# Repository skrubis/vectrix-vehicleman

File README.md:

# vectrix-vehicleman
Vectrix VX1 BMS manager + TC charger control + LTE connectivity + GPS tracker + Alarm + whatever else time can solve.

meant to be used together with Openinverter Flying ADC BMS

Includes:

 - ESP32 + SD card
  - Battery backup with charger for esp + LTE (1x18650)
   - Footprint for GigaVESC HV (150-180V?)@2~3A(?) -> 12V [DCDC](https://github.com/kaminaris/GigaESC/tree/master/PowerBoard/TL494V2OC)
   - LTE modem (SIM7070G with GNSS) + 1 SIM
   - 1x CAN TWAI transceiver
   - 2x CAN SPI transceiver (in case TC charger(s) are on the same address or say multiple R4850G2 are used)
   - A few relays and mosfets for external loads
   - Accelerometer/IMU for "alarm" functionality
   - Moisture/temp sensor for condensation detection (?)
   - RTC
   -TYPE 2 charging CP PP control
   - External antenna PCB for active GNSS + passive LTE should be here as well.

NOT TESTED, NOT VERIFIED!
CC-BY-NC 4.0

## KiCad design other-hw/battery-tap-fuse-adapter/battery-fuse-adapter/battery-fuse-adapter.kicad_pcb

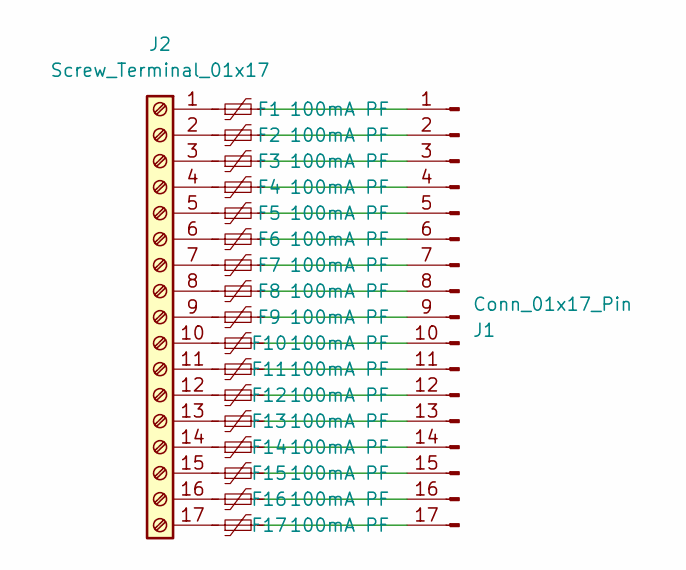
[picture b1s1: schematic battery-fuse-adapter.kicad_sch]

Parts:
F1, F2, F3, F4, F5, F6, F7, F8, F9, F10, F11, F12, F13, F14, F15, F16, F17: 100mA PF; Fuse_0603_1608Metric; LCSC C369142
J1: Conn_01x17_Pin; PinHeader_1x17_P2.54mm_Vertical
J2: Screw_Terminal_01x17; C430372; LCSC C430372

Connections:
unnamed: F1.2, J1.1
unnamed: F2.2, J1.2
unnamed: F3.2, J1.3
unnamed: F4.2, J1.4
unnamed: F5.2, J1.5
unnamed: F6.2, J1.6
unnamed: F7.2, J1.7
unnamed: F8.2, J1.8
unnamed: F9.2, J1.9
unnamed: F10.2, J1.10
unnamed: F11.2, J1.11
unnamed: F12.2, J1.12
unnamed: F13.2, J1.13
unnamed: F14.2, J1.14
unnamed: F15.2, J1.15
unnamed: F16.2, J1.16
unnamed: F17.2, J1.17
unnamed: F1.1, J2.1
unnamed: F2.1, J2.2
unnamed: F3.1, J2.3
unnamed: F4.1, J2.4
unnamed: F5.1, J2.5
unnamed: F6.1, J2.6
unnamed: F7.1, J2.7
unnamed: F8.1, J2.8
unnamed: F9.1, J2.9
unnamed: F10.1, J2.10
unnamed: F11.1, J2.11
unnamed: F12.1, J2.12
unnamed: F13.1, J2.13
unnamed: F14.1, J2.14
unnamed: F15.1, J2.15
unnamed: F16.1, J2.16
unnamed: F17.1, J2.17

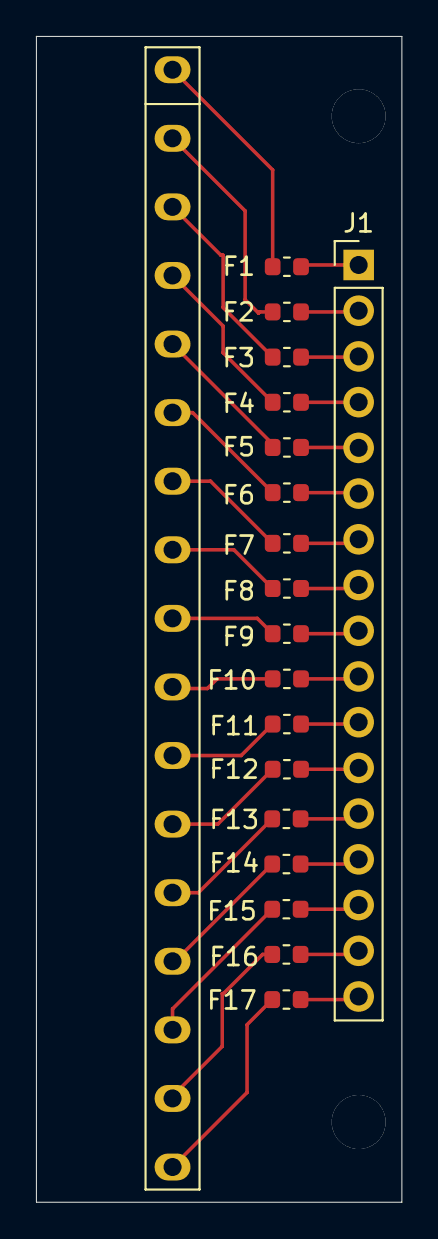
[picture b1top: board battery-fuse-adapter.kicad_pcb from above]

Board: 2 copper layers, 20.3 x 64.8 mm, 19 parts (0 on the bottom side), 34 nets.

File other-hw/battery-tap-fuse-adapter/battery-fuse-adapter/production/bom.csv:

Designator,Footprint,Quantity,Value,LCSC Part #
"F1, F10, F11, F12, F13, F14, F15, F16, F17, F2, F3, F4, F5, F6, F7, F8, F9",0603,17,100mA PF,C369142
J2,C430372,1,Screw_Terminal_01x17,C430372

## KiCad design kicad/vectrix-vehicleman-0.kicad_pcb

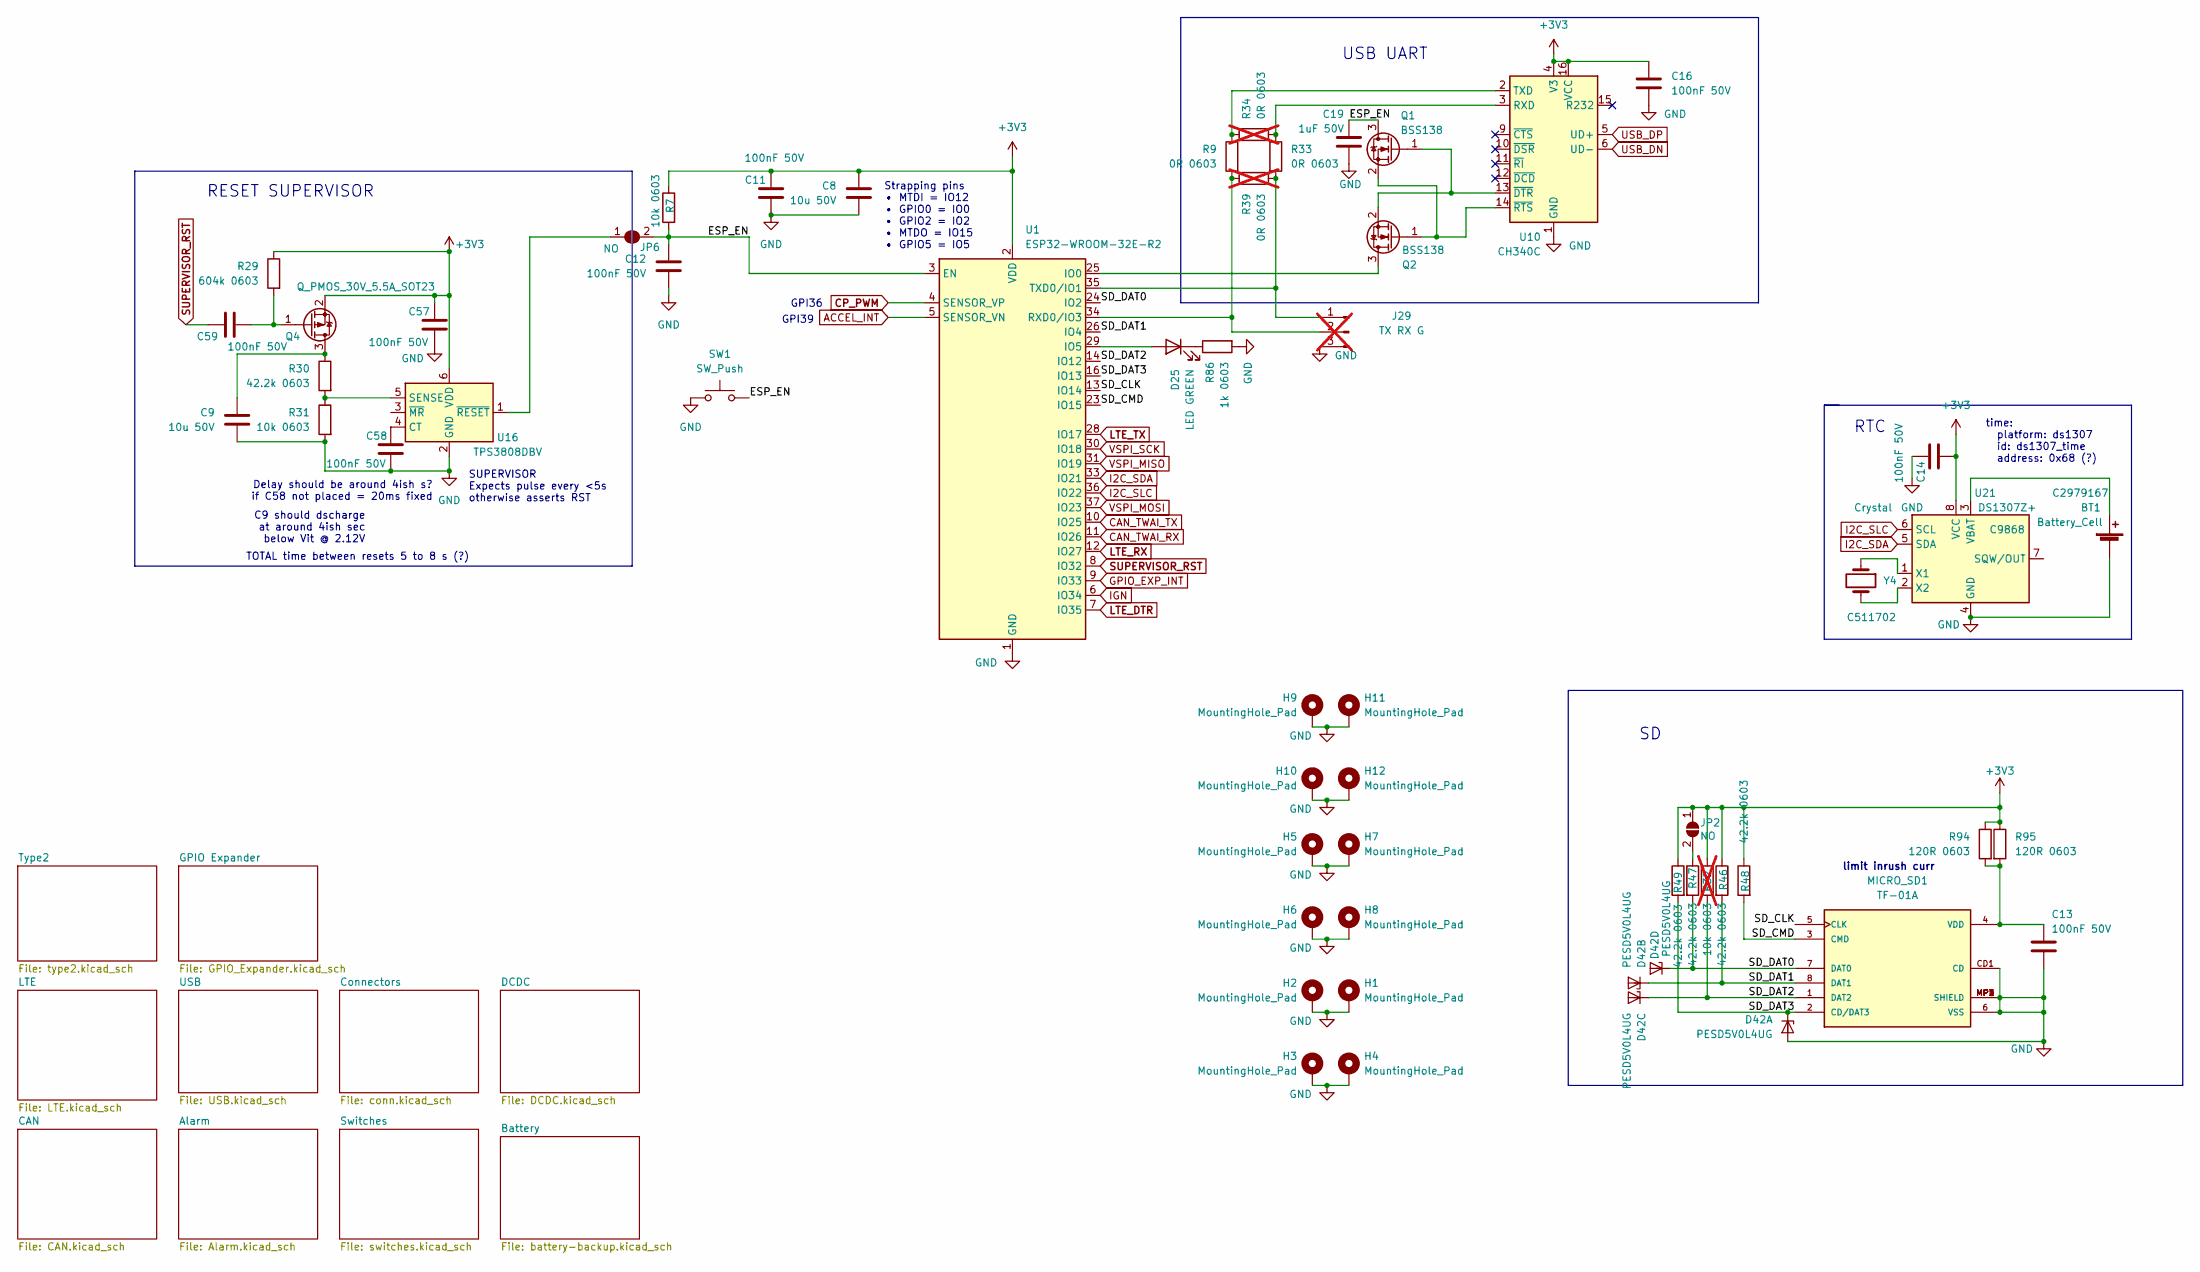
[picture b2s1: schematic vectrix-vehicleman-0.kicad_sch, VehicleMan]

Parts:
BT1: Battery_Cell; BatteryHolder_MYOUNG_BS-07-A1BJ001_CR2032; LCSC C2979167
C8, C9: 10u 50V; C_1206_3216Metric; LCSC C13585
C11, C12, C13, C14, C16, C57, C58, C59: 100nF 50V; C_0603_1608Metric; LCSC C14663
C19: 1uF 50V; C_0603_1608Metric; LCSC C6119852
D25: LED GREEN; LED_0805_2012Metric; LCSC C5875740
D42: PESD5V0L4UG; SOT-353_SC-70-5; LCSC C5116450
H1, H2, H3, H4, H5, H6, H7, H8, H9, H10, H11, H12: MountingHole_Pad; MountingHole_3.2mm_M3_DIN965_Pad_TopBottom
J29: TX RX G; PinHeader_1x03_P1.27mm_Vertical; not fitted
JP2, JP6: NO; SolderJumper-2_P1.3mm_Open_TrianglePad1.0x1.5mm
MICRO_SD1: TF-01A; LCSC C91145
Q1, Q2: BSS138; SOT-23; LCSC C112239
Q4: Q_PMOS_30V_5.5A_SOT23; SOT-23; LCSC C105162
R7, R31: 10k 0603; R_0603_1608Metric; LCSC C2930027
R9, R33: 0R 0603; R_0603_1608Metric; LCSC C21189
R29: 604k 0603; R_0603_1608Metric; LCSC C2933246
R30, R46, R47, R48, R49: 42.2k 0603; R_0603_1608Metric; LCSC C5126245
R32: 10k 0603; R_0603_1608Metric; LCSC C2930027; not fitted
R34, R39: 0R 0603; R_0603_1608Metric; LCSC C21189; not fitted
R86: 1k 0603; R_0603_1608Metric; LCSC C2907113
R94, R95: 120R 0603; R_0603_1608Metric; LCSC C22787
SW1: SW_Push; SW_PUSH_6mm; LCSC C455095
U1: ESP32-WROOM-32E-R2; ESP32-WROOM-32D; LCSC C82899
U10: CH340C; SOIC-16_3.9x9.9mm_P1.27mm; LCSC C84681
U16: TPS3808DBV; SOT-23-6; LCSC C19653
U21: DS1307Z+; SOIC-8_3.9x4.9mm_P1.27mm; LCSC C9868
Y4: Crystal; Crystal_DS26_D2.0mm_L6.0mm_Horizontal; LCSC C511702

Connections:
+3V3: C8.1, C11.1, C14.2, C16.1, C57.1, JP2.1 (A), Q4.2 (S), R7.1, R29.1, R32.1, R46.1, R48.1, R49.1, R94.1, R95.1, U1.2 (VDD), U10.4 (V3), U10.16 (VCC), U16.6 (VDD), U21.8 (VCC); also elsewhere on the board
/ESP_EN: C12.1, C19.1, JP6.2 (B), Q1.3 (D), R7.2, SW1.2, U1.3 (EN)
/SD_CLK: MICRO_SD1.5 (CLK), U1.13 (IO14)
/SD_CMD: MICRO_SD1.3 (CMD), R48.2, U1.23 (IO15)
/SD_DAT0: D42.5 (K4), MICRO_SD1.7 (DAT0), R47.2, U1.24 (IO2)
/SD_DAT1: D42.3 (K2), MICRO_SD1.8 (DAT1), R46.2, U1.26 (IO4)
/SD_DAT2: D42.4 (K3), MICRO_SD1.1 (DAT2), R32.2, U1.14 (IO12)
/SD_DAT3: D42.1 (K1), MICRO_SD1.2 (CD/DAT3), R49.2, U1.16 (IO13)
ACCEL_INT: U1.5 (SENSOR_VN); also elsewhere on the board
CAN_TWAI_RX: U1.11 (IO26); also elsewhere on the board
CAN_TWAI_TX: U1.10 (IO25); also elsewhere on the board
CP_PWM: U1.4 (SENSOR_VP); also elsewhere on the board
GND: BT1.2 (-), C8.2, C9.2, C11.2, C12.2, C13.2, C14.1, C16.2, C19.2, C57.2, C58.2, D42.2 (A), H1.1, H2.1, H3.1, H4.1, H5.1, H6.1, H7.1, H8.1, H9.1, H10.1, H11.1, H12.1, J29.3, MICRO_SD1.6 (VSS), MICRO_SD1.CD1 (CD), MICRO_SD1.MP1 (SHIELD), MICRO_SD1.MP2 (SHIELD), MICRO_SD1.MP3 (SHIELD), MICRO_SD1.MP4 (SHIELD), R31.2, R86.2, SW1.1, U1.1 (GND), U1.15 (GND), U1.38 (GND), U1.39 (GND), U10.1 (GND), U16.2 (GND), U21.4 (GND); also elsewhere on the board
GPIO_EXP_INT: U1.9 (IO33); also elsewhere on the board
I2C_SDA: U1.33 (IO21), U21.5 (SDA); also elsewhere on the board
I2C_SLC: U1.36 (IO22), U21.6 (SCL); also elsewhere on the board
IGN: U1.6 (IO34); also elsewhere on the board
LTE_DTR: U1.7 (IO35); also elsewhere on the board
LTE_RX: U1.12 (IO27); also elsewhere on the board
LTE_TX: U1.28 (IO17); also elsewhere on the board
unnamed: BT1.1 (+), U21.3 (VBAT)
unnamed: D25.2 (A), U1.29 (IO5)
unnamed: D25.1 (K), R86.1
unnamed: J29.1, R33.2, R39.2, U1.35 (TXD0/IO1)
unnamed: J29.2, R9.2, R39.1, U1.34 (RXD0/IO3)
unnamed: JP2.2 (B), R47.1
unnamed: JP6.1 (A), U16.1 (~RESET)
unnamed: C13.1, MICRO_SD1.4 (VDD), R94.2, R95.2
unnamed: Q1.1 (G), Q2.2 (S), U10.13 (~DTR)
unnamed: Q1.2 (S), Q2.1 (G), U10.14 (~RTS)
unnamed: Q2.3 (D), U1.25 (IO0)
unnamed: C9.1, Q4.3 (D), R30.1
unnamed: C59.2, Q4.1 (G), R29.2
unnamed: R33.1, R34.2, U10.3 (RXD)
unnamed: R9.1, R34.1, U10.2 (TXD)
unnamed: C58.1, U16.4 (CT)
unnamed: R30.2, R31.1, U16.5 (SENSE)
unnamed: U21.1 (X1), Y4.1
unnamed: U21.2 (X2), Y4.2
SUPERVISOR_RST: C59.1, U1.8 (IO32)
USB_DN: U10.6 (UD-); also elsewhere on the board
USB_DP: U10.5 (UD+); also elsewhere on the board
VSPI_MISO: U1.31 (IO19); also elsewhere on the board
VSPI_MOSI: U1.37 (IO23); also elsewhere on the board
VSPI_SCK: U1.30 (IO18); also elsewhere on the board

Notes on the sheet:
C9 should dscharge at around 4ish sec below Vit @ 2.12V
SUPERVISOR Expects pulse every <5s otherwise asserts RST
limit inrush curr
TOTAL time between resets 5 to 8 s (?)
RTC
GPI39
GPI36
USB UART
RESET SUPERVISOR
Strapping pins • MTDI = IO12 • GPIO0 = IO0 • GPIO2 = IO2 • MTDO = IO15 • GPIO5 = IO5
time: platform: ds1307 id: ds1307_time address: 0x68 (?)
Delay should be around 4ish s? if C58 not placed = 20ms fixed

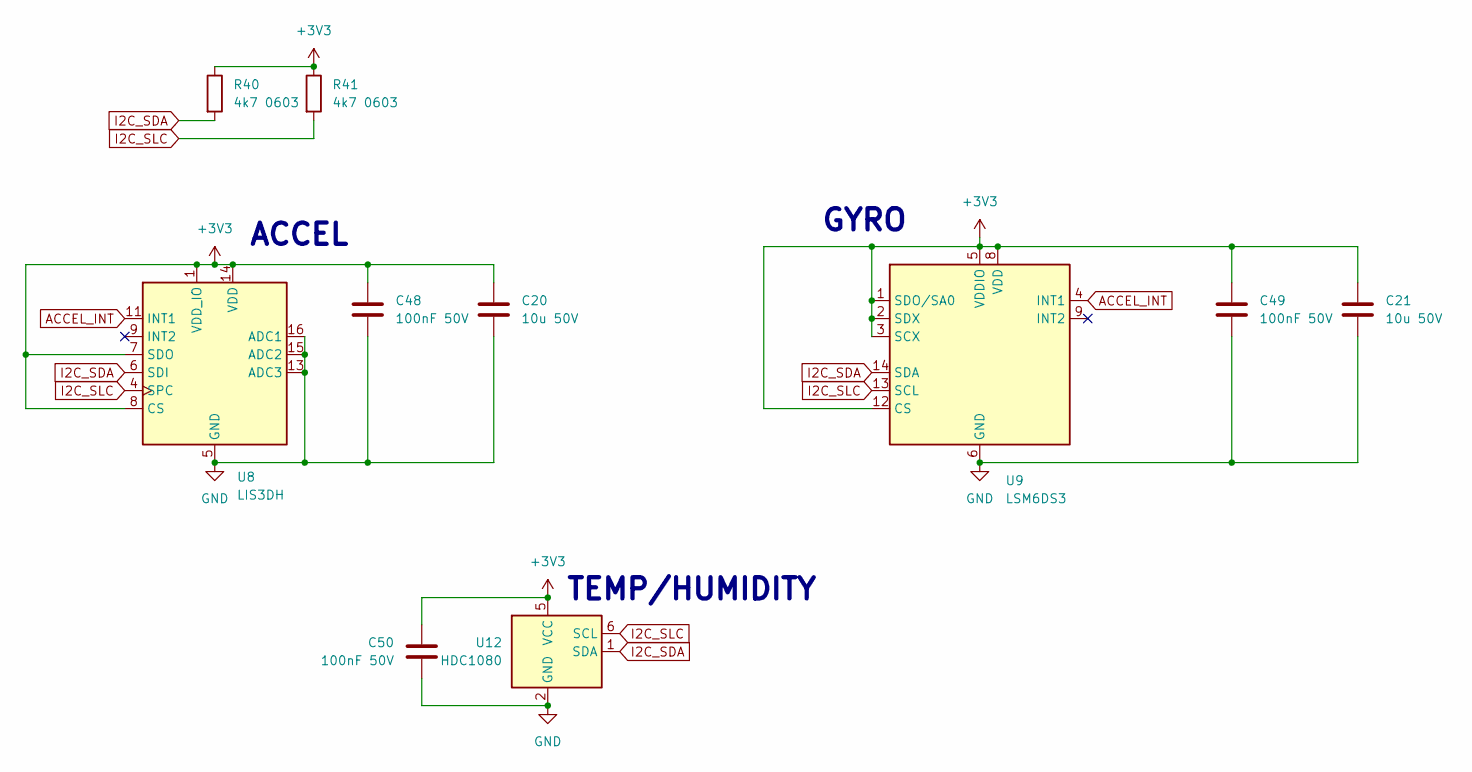
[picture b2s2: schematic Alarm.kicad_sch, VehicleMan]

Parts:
C20, C21: 10u 50V; C_1206_3216Metric; LCSC C13585
C48, C49, C50: 100nF 50V; C_0603_1608Metric; LCSC C14663
R40, R41: 4k7 0603; R_0603_1608Metric; LCSC C99782
U8: LIS3DH; LGA-16_3x3mm_P0.5mm_LayoutBorder3x5y; LCSC C15134
U9: LSM6DS3; LGA-14_3x2.5mm_P0.5mm_LayoutBorder3x4y; LCSC C967633
U12: HDC1080; Texas_PWSON-N6; LCSC C82227

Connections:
+3V3: C20.1, C21.1, C48.1, C49.1, C50.1, R40.1, R41.1, U8.1 (VDD_IO), U8.7 (SDO), U8.8 (CS), U8.14 (VDD), U9.1 (SDO/SA0), U9.2 (SDX), U9.3 (SCX), U9.5 (VDDIO), U9.8 (VDD), U9.12 (CS), U12.5 (VCC); also elsewhere on the board
ACCEL_INT: U8.11 (INT1), U9.4 (INT1); also elsewhere on the board
GND: C20.2, C21.2, C48.2, C49.2, C50.2, U8.5 (GND), U8.10 (GND), U8.12 (GND), U8.13 (ADC3), U8.15 (ADC2), U8.16 (ADC1), U9.6 (GND), U9.7 (GND), U12.2 (GND); also elsewhere on the board
I2C_SDA: R40.2, U8.6 (SDI), U9.14 (SDA), U12.1 (SDA); also elsewhere on the board
I2C_SLC: R41.2, U8.4 (SPC), U9.13 (SCL), U12.6 (SCL); also elsewhere on the board

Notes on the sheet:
ACCEL
GYRO
TEMP/HUMIDITY

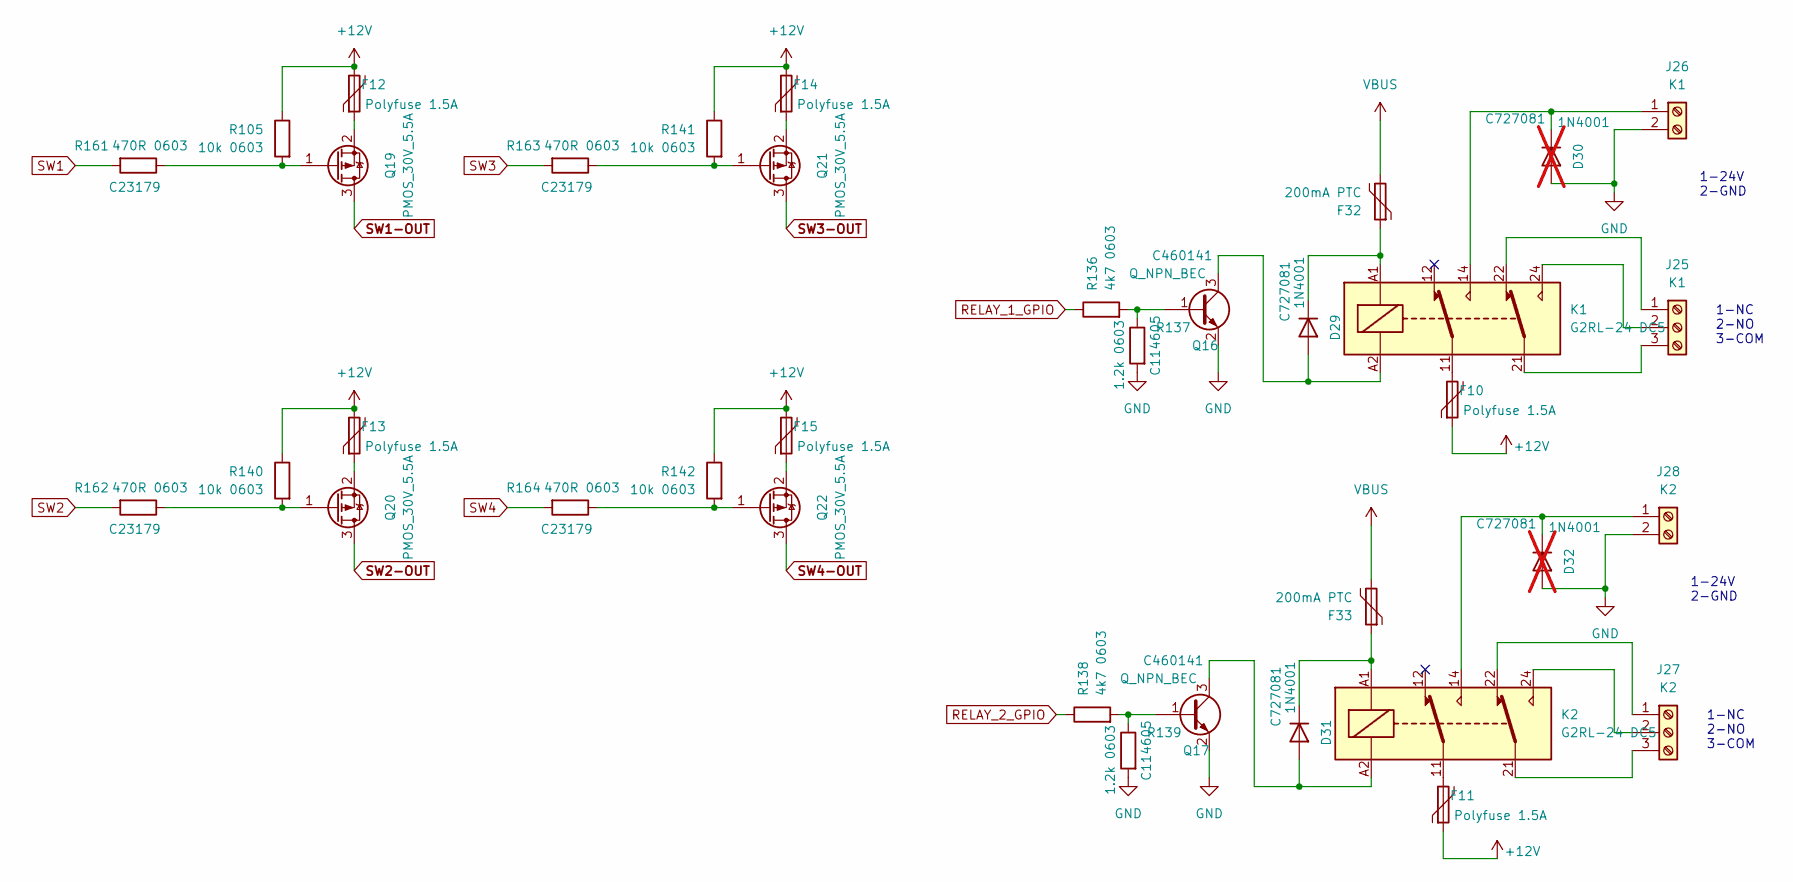
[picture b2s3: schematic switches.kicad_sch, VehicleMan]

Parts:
D29, D31: 1N4001; D_SMA; LCSC C727081
D30, D32: 1N4001; D_SMA; LCSC C727081; not fitted
F10, F11, F12, F13, F14, F15: Polyfuse 1.5A; Fuse_1812_4532Metric; LCSC C883154
F32, F33: 200mA PTC; Fuse_0805_2012Metric; LCSC C2840556
J25: K1; TerminalBlock_4Ucon_1x03_P3.50mm_Horizontal; LCSC C695630
J26: K1; TerminalBlock_4Ucon_1x02_P3.50mm_Horizontal; LCSC C695629
J27: K2; TerminalBlock_4Ucon_1x03_P3.50mm_Horizontal; LCSC C695630
J28: K2; TerminalBlock_4Ucon_1x02_P3.50mm_Horizontal; LCSC C695629
K1, K2: G2RL-24 DC5; Relay_DPDT_Omron_G2RL-2; LCSC C6866153
Q16, Q17: Q_NPN_BEC; SOT-23; LCSC C460141
Q19, Q20, Q21, Q22: PMOS_30V_5.5A; SOT-23; LCSC C105162
R105, R140, R141, R142: 10k 0603; R_0603_1608Metric; LCSC C2930027
R136, R138: 4k7 0603; R_0603_1608Metric; LCSC C99782
R137, R139: 1.2k 0603; R_0603_1608Metric; LCSC C114605
R161, R162, R163, R164: 470R 0603; R_0603_1608Metric; LCSC C23179

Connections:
+12V: F10.1, F11.1, F12.2, F13.2, F14.2, F15.2, R105.1, R140.1, R141.1, R142.1; also elsewhere on the board
GND: D30.2 (A), D32.2 (A), J26.2, J28.2, Q16.2 (E), Q17.2 (E), R137.2, R139.2; also elsewhere on the board
unnamed: D29.2 (A), K1.A2, Q16.3 (C)
unnamed: D29.1 (K), F32.1, K1.A1
unnamed: D30.1 (K), J26.1, K1.14
unnamed: D31.2 (A), K2.A2, Q17.3 (C)
unnamed: D31.1 (K), F33.1, K2.A1
unnamed: D32.1 (K), J28.1, K2.14
unnamed: F10.2, K1.11
unnamed: F11.2, K2.11
unnamed: J25.1, K1.22
unnamed: J25.2, K1.24
unnamed: J25.3, K1.21
unnamed: J27.1, K2.22
unnamed: J27.2, K2.24
unnamed: J27.3, K2.21
unnamed: Q16.1 (B), R136.2, R137.1
unnamed: Q17.1 (B), R138.2, R139.1
unnamed: Q19.1 (G), R105.2, R161.1
unnamed: F12.1, Q19.2 (S)
unnamed: Q20.1 (G), R140.2, R162.1
unnamed: F13.1, Q20.2 (S)
unnamed: Q21.1 (G), R141.2, R163.1
unnamed: F14.1, Q21.2 (S)
unnamed: Q22.1 (G), R142.2, R164.1
unnamed: F15.1, Q22.2 (S)
RELAY_1_GPIO: R136.1; also elsewhere on the board
RELAY_2_GPIO: R138.1; also elsewhere on the board
SW1: R161.2; also elsewhere on the board
SW1-OUT: Q19.3 (D); also elsewhere on the board
SW2: R162.2; also elsewhere on the board
SW2-OUT: Q20.3 (D); also elsewhere on the board
SW3: R163.2; also elsewhere on the board
SW3-OUT: Q21.3 (D); also elsewhere on the board
SW4: R164.2; also elsewhere on the board
SW4-OUT: Q22.3 (D); also elsewhere on the board
VBUS: F32.2, F33.2; also elsewhere on the board

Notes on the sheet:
1-NC 2-NO 3-COM
1-24V 2-GND

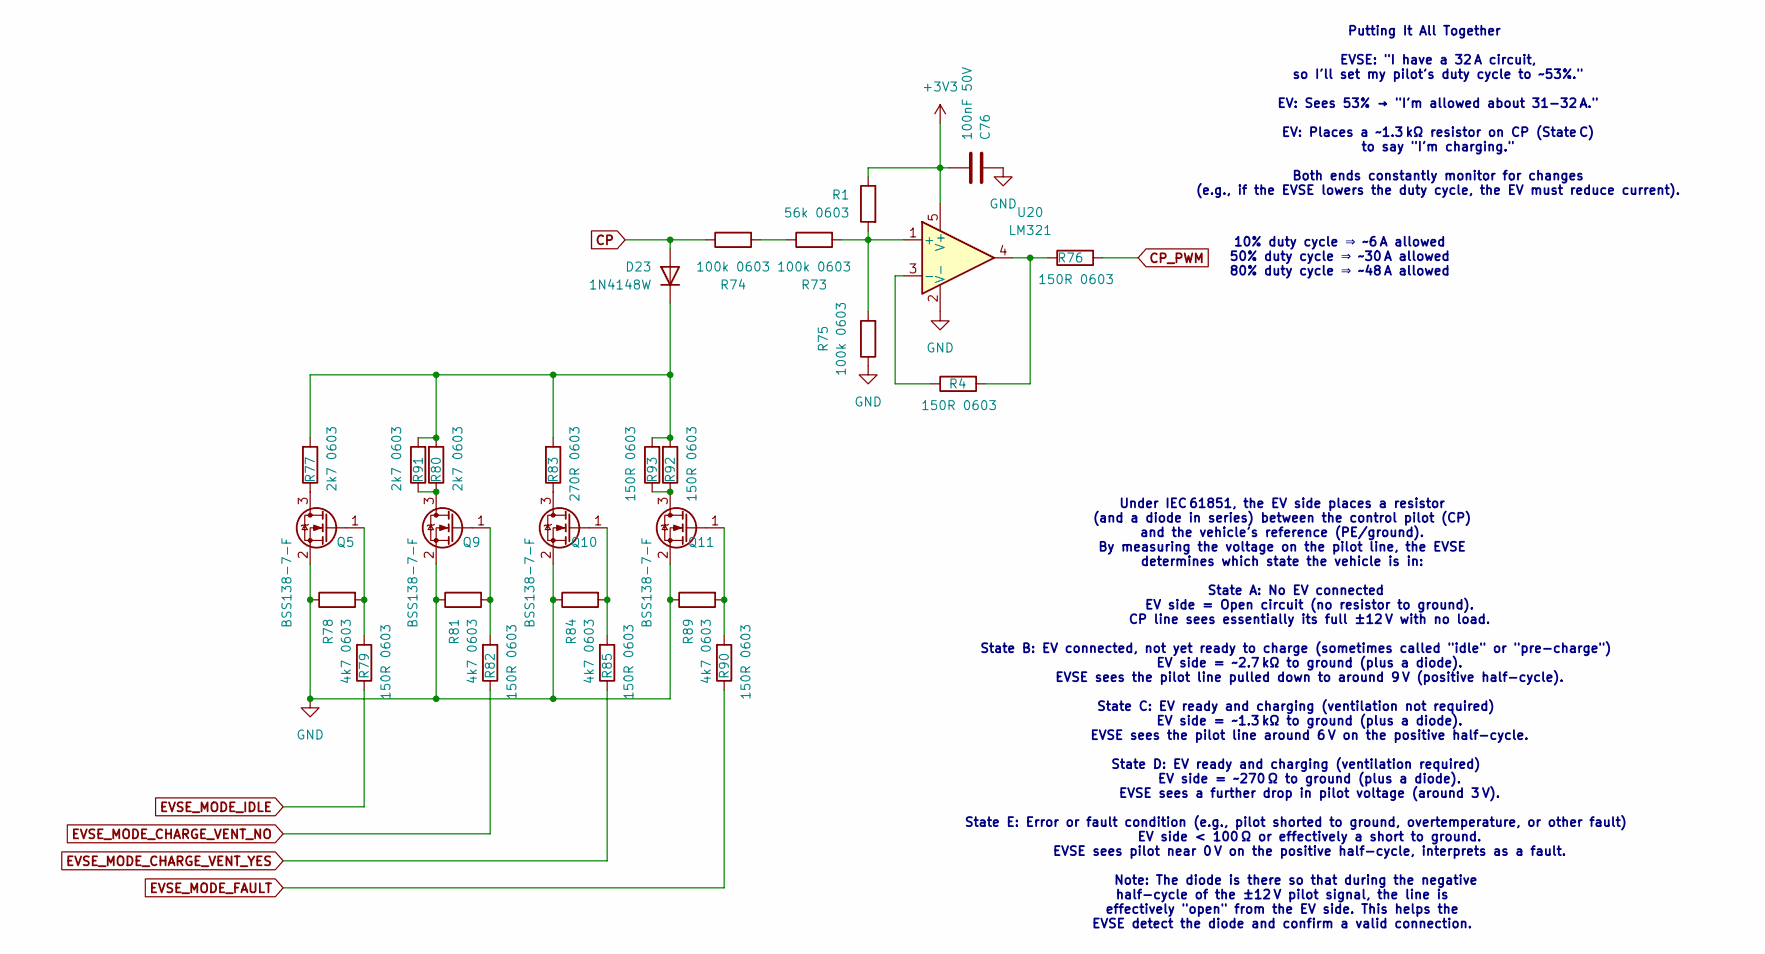
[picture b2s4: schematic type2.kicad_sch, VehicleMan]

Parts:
C76: 100nF 50V; C_0603_1608Metric; LCSC C14663
D23: 1N4148W; D_SOD-123; LCSC C917030
Q5, Q9, Q10, Q11: BSS138-7-F; SOT-23; LCSC C40912
R1: 56k 0603; R_0603_1608Metric; LCSC C23206
R4, R76, R79, R82, R85, R90, R92, R93: 150R 0603; R_0603_1608Metric; LCSC C2907103
R73, R74, R75: 100k 0603; R_0603_1608Metric; LCSC C14675
R77, R80, R91: 2k7 0603; R_0603_1608Metric; LCSC C13167
R78, R81, R84, R89: 4k7 0603; R_0603_1608Metric; LCSC C99782
R83: 270R 0603; R_0603_1608Metric; LCSC C22966
U20: LM321; SOT-23-5; LCSC C668208

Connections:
+3V3: C76.2, R1.1, U20.5 (V+); also elsewhere on the board
CP: D23.2 (A), R74.1; also elsewhere on the board
CP_PWM: R76.2; also elsewhere on the board
EVSE_MODE_CHARGE_VENT_NO: R82.1
EVSE_MODE_CHARGE_VENT_YES: R85.1
EVSE_MODE_FAULT: R90.1
EVSE_MODE_IDLE: R79.1
GND: C76.1, Q5.2 (S), Q9.2 (S), Q10.2 (S), Q11.2 (S), R75.1, R78.1, R81.1, R84.1, R89.1, U20.2 (V-); also elsewhere on the board
unnamed: D23.1 (K), R77.2, R80.2, R83.2, R91.2, R92.2, R93.2
unnamed: Q5.3 (D), R77.1
unnamed: Q5.1 (G), R78.2, R79.2
unnamed: Q9.3 (D), R80.1, R91.1
unnamed: Q9.1 (G), R81.2, R82.2
unnamed: Q10.3 (D), R83.1
unnamed: Q10.1 (G), R84.2, R85.2
unnamed: Q11.3 (D), R92.1, R93.1
unnamed: Q11.1 (G), R89.2, R90.2
unnamed: R4.2, R76.1, U20.4
unnamed: R73.1, R74.2
unnamed: R1.2, R73.2, R75.2, U20.1 (+)
unnamed: R4.1, U20.3 (-)

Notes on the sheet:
Under IEC 61851, the EV side places a resistor (and a diode in series) between the control pilot (CP) and the vehicle's reference (PE/ground). By measuring the voltage on the pilot line, the EVSE determines which state the vehicle is in: State A: No EV connected EV side = Open circuit (no resistor 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
10% duty cycle ⇒ ~6 A allowed 50% duty cycle ⇒ ~30 A allowed 80% duty cycle ⇒ ~48 A allowed
Putting It All Together EVSE: "I have a 32 A circuit, so I'll set my pilot's duty cycle to ~53%." EV: Sees 53% → "I'm allowed about 31-32 A." EV: Places a ~1.3 kΩ resistor on CP (State C) to say "I'm charging." Both ends constantly monitor for changes (e.g., if the EVSE lowers the duty cycle, the E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

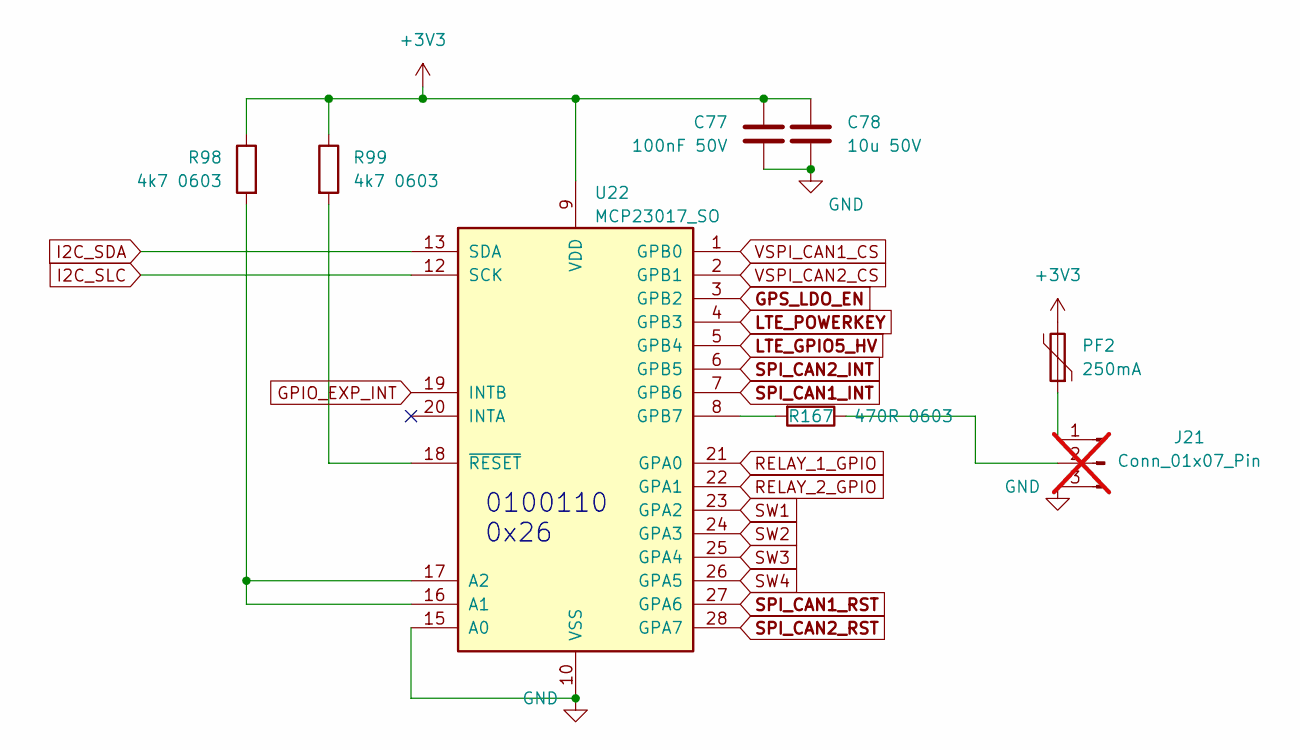
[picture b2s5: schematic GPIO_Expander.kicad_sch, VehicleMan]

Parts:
C77: 100nF 50V; C_0603_1608Metric; LCSC C14663
C78: 10u 50V; C_1206_3216Metric; LCSC C13585
J21: Conn_01x07_Pin; PinHeader_1x03_P1.27mm_Vertical; not fitted
PF2: 250mA; Fuse_1206_3216Metric; LCSC C70065
R98, R99: 4k7 0603; R_0603_1608Metric; LCSC C99782
R167: 470R 0603; R_0603_1608Metric; LCSC C23179
U22: MCP23017_SO; SOIC-28W_7.5x17.9mm_P1.27mm; LCSC C629440

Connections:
+3V3: C77.1, C78.1, PF2.2, R98.1, R99.1, U22.9 (VDD); also elsewhere on the board
GND: C77.2, C78.2, J21.3, U22.10 (VSS), U22.15 (A0); also elsewhere on the board
GPIO_EXP_INT: U22.19 (INTB); also elsewhere on the board
GPS_LDO_EN: U22.3 (GPB2); also elsewhere on the board
I2C_SDA: U22.13 (SDA); also elsewhere on the board
I2C_SLC: U22.12 (SCK); also elsewhere on the board
LTE_GPIO5_HV: U22.5 (GPB4); also elsewhere on the board
LTE_POWERKEY: U22.4 (GPB3); also elsewhere on the board
unnamed: J21.1, PF2.1
unnamed: J21.2, R167.1
unnamed: R98.2, U22.16 (A1), U22.17 (A2)
unnamed: R167.2, U22.8 (GPB7)
unnamed: R99.2, U22.18 (~RESET)
RELAY_1_GPIO: U22.21 (GPA0); also elsewhere on the board
RELAY_2_GPIO: U22.22 (GPA1); also elsewhere on the board
SPI_CAN1_INT: U22.7 (GPB6); also elsewhere on the board
SPI_CAN1_RST: U22.27 (GPA6); also elsewhere on the board
SPI_CAN2_INT: U22.6 (GPB5); also elsewhere on the board
SPI_CAN2_RST: U22.28 (GPA7); also elsewhere on the board
SW1: U22.23 (GPA2); also elsewhere on the board
SW2: U22.24 (GPA3); also elsewhere on the board
SW3: U22.25 (GPA4); also elsewhere on the board
SW4: U22.26 (GPA5); also elsewhere on the board
VSPI_CAN1_CS: U22.1 (GPB0); also elsewhere on the board
VSPI_CAN2_CS: U22.2 (GPB1); also elsewhere on the board

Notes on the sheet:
0100110 0x26

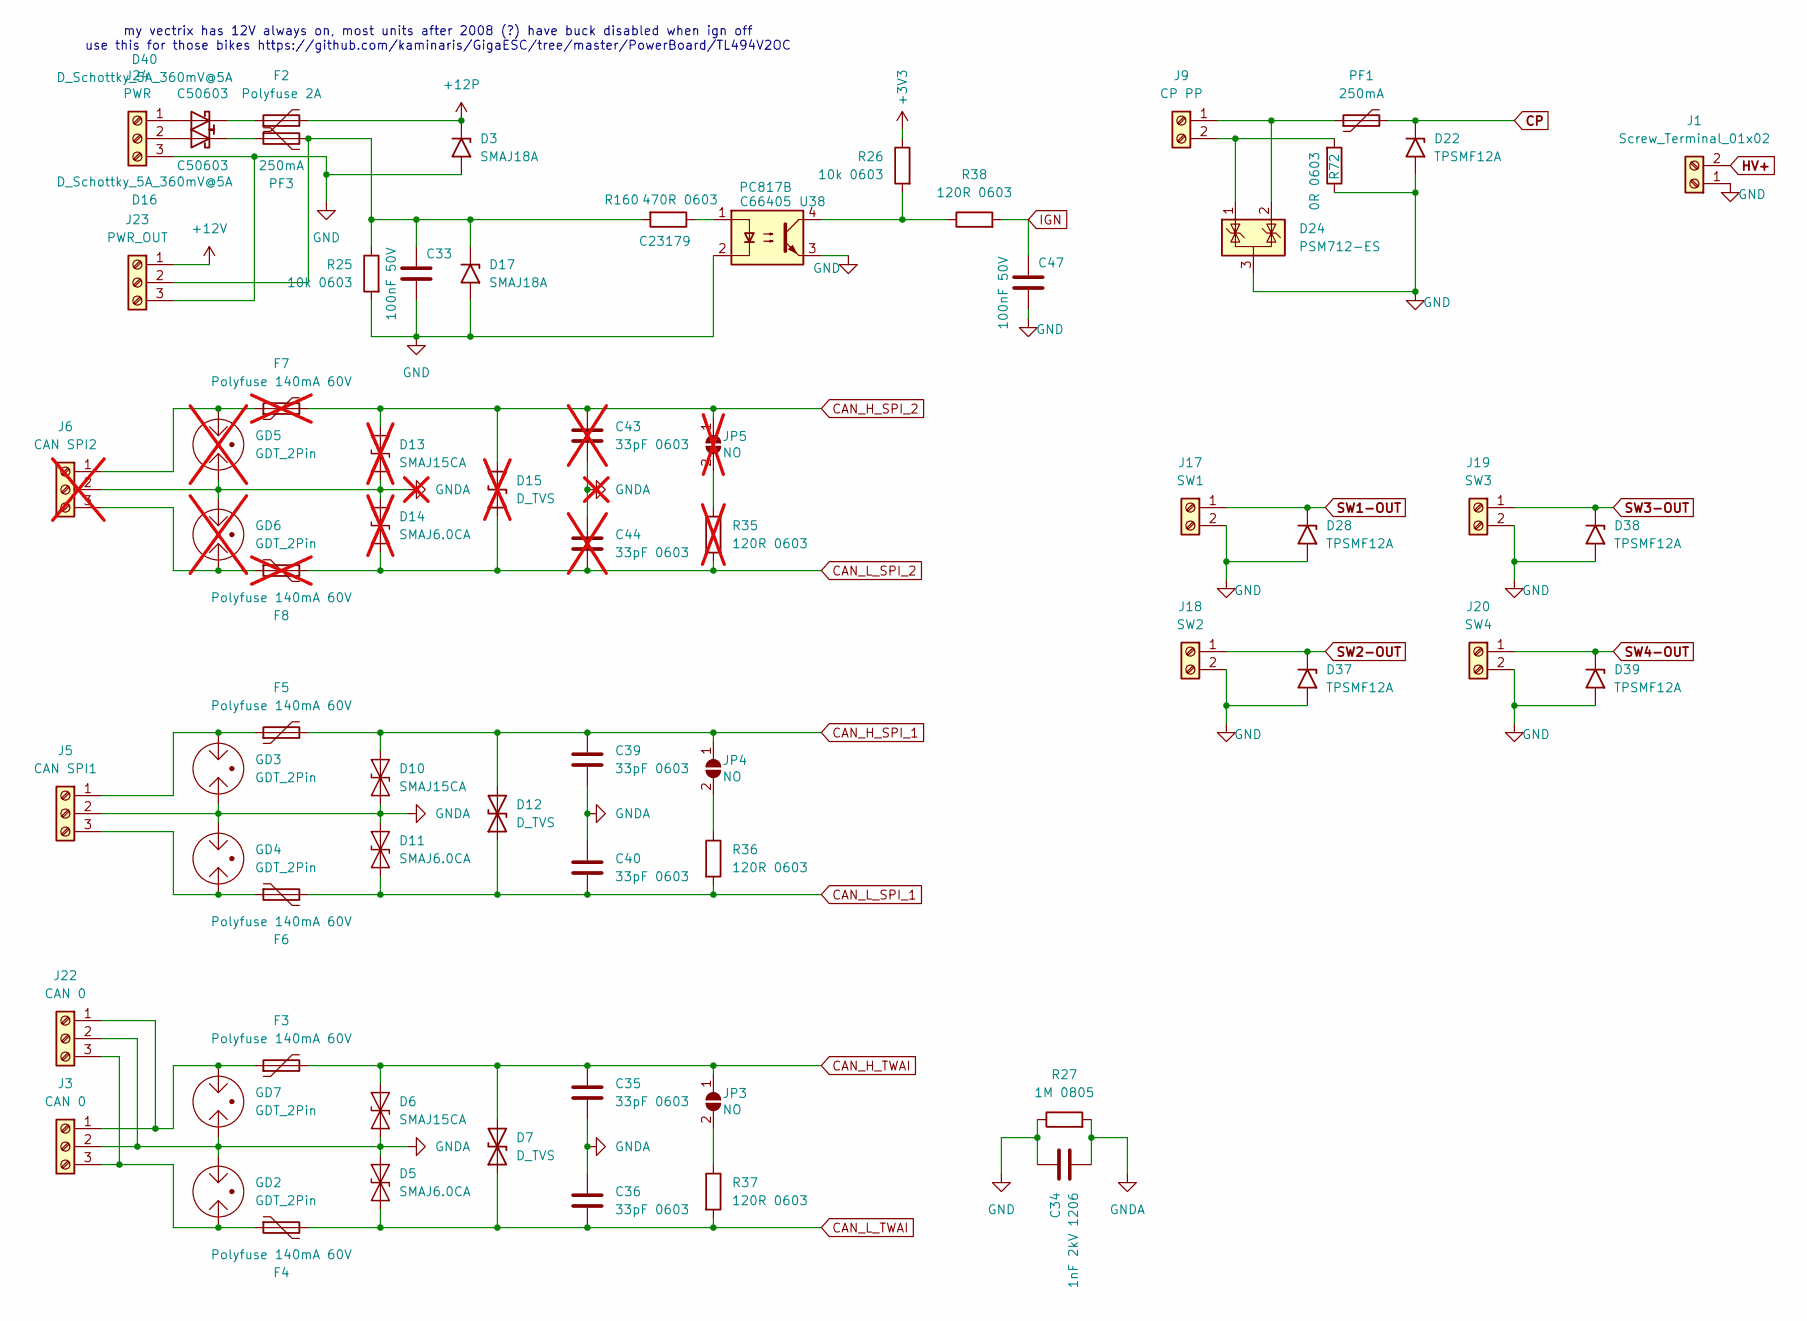
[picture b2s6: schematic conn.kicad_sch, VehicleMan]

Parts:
C33, C47: 100nF 50V; C_0603_1608Metric; LCSC C14663
C34: 1nF 2kV 1206; C_1206_3216Metric; LCSC C9196
C35, C36, C39, C40: 33pF 0603; C_0603_1608Metric; LCSC C107047
C43, C44: 33pF 0603; C_0603_1608Metric; LCSC C107047; not fitted
D3, D17: SMAJ18A; D_SMA
D5, D11: SMAJ6.0CA; D_SMA; LCSC C134999
D6, D10: SMAJ15CA; D_SMA; LCSC C2848698
D7, D12: D_TVS; D_SOD-323; LCSC C41409313
D13: SMAJ15CA; D_SMA; LCSC C2848698; not fitted
D14: SMAJ6.0CA; D_SMA; LCSC C134999; not fitted
D15: D_TVS; D_SOD-323; LCSC C41409313; not fitted
D16, D40: D_Schottky_5A_360mV@5A; D_SOD-128; LCSC C50603
D22, D28, D37, D38, D39: TPSMF12A; D_SOD-123; LCSC C42440530
D24: PSM712-ES; SOT-23; LCSC C5180294
F2: Polyfuse 2A; Fuse_2920_7451Metric; LCSC C6165181
F3, F4, F5, F6: Polyfuse 140mA 60V; Fuse_1812_4532Metric; LCSC C20994
F7, F8: Polyfuse 140mA 60V; Fuse_1812_4532Metric; LCSC C20994; not fitted
GD2, GD3, GD4, GD7: GDT_2Pin; Fuse_1812_4532Metric; LCSC C9235
GD5, GD6: GDT_2Pin; Fuse_1812_4532Metric; LCSC C9235; not fitted
J1: Screw_Terminal_01x02; TerminalBlock_Phoenix_MKDS-1,5-2-5.08_1x02_P5.08mm_Horizont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; LCSC C8465
J3, J22: CAN 0; TerminalBlock_4Ucon_1x03_P3.50mm_Horizontal; LCSC C695630
J5: CAN SPI1; TerminalBlock_4Ucon_1x03_P3.50mm_Horizontal; LCSC C695630
J6: CAN SPI2; TerminalBlock_4Ucon_1x03_P3.50mm_Horizontal; LCSC C695630; not fitted
J9: CP PP; TerminalBlock_4Ucon_1x02_P3.50mm_Horizontal; LCSC C695629
J17: SW1; TerminalBlock_4Ucon_1x02_P3.50mm_Horizontal; LCSC C695629
J18: SW2; TerminalBlock_4Ucon_1x02_P3.50mm_Horizontal; LCSC C695629
J19: SW3; TerminalBlock_4Ucon_1x02_P3.50mm_Horizontal; LCSC C695629
J20: SW4; TerminalBlock_4Ucon_1x02_P3.50mm_Horizontal; LCSC C695629
J23: PWR_OUT; TerminalBlock_4Ucon_1x03_P3.50mm_Horizontal; LCSC C695630
J24: PWR; TerminalBlock_4Ucon_1x03_P3.50mm_Horizontal; LCSC C695630
JP3, JP4: NO; SolderJumper-2_P1.3mm_Open_TrianglePad1.0x1.5mm
JP5: NO; SolderJumper-2_P1.3mm_Open_TrianglePad1.0x1.5mm; not fitted
PF1, PF3: 250mA; Fuse_1206_3216Metric; LCSC C70065
R25, R26: 10k 0603; R_0603_1608Metric; LCSC C2930027
R27: 1M 0805; R_0805_2012Metric; LCSC C17514
R35: 120R 0603; R_0603_1608Metric; LCSC C22787; not fitted
R36, R37, R38: 120R 0603; R_0603_1608Metric; LCSC C22787
R72: 0R 0603; R_0603_1608Metric; LCSC C21189
R160: 470R 0603; R_0603_1608Metric; LCSC C23179
U38: PC817B; SMDIP-4_W7.62mm; LCSC C66405

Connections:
+3V3: R26.1; also elsewhere on the board
+12P: D3.1 (A1), F2.2; also elsewhere on the board
+12V: J23.1; also elsewhere on the board
CAN_H_SPI_1: C39.1, D10.2 (A2), D12.2 (A2), F5.2, JP4.1 (A); also elsewhere on the board
CAN_H_SPI_2: C43.1, D13.2 (A2), D15.2 (A2), F7.2, JP5.1 (A); also elsewhere on the board
CAN_H_TWAI: C35.1, D6.2 (A2), D7.2 (A2), F3.2, JP3.1 (A); also elsewhere on the board
CAN_L_SPI_1: C40.2, D11.1 (A1), D12.1 (A1), F6.2, R36.2; also elsewhere on the board
CAN_L_SPI_2: C44.2, D14.1 (A1), D15.1 (A1), F8.2, R35.2; also elsewhere on the board
CAN_L_TWAI: C36.2, D5.1 (A1), D7.1 (A1), F4.2, R37.2; also elsewhere on the board
CP: D22.1 (A1), PF1.2; also elsewhere on the board
GND: C33.2, C34.1, C47.2, D3.2 (A2), D17.2 (A2), D22.2 (A2), D24.3 (A), D28.2 (A2), D37.2 (A2), D38.2 (A2), D39.2 (A2), J1.1, J17.2, J18.2, J19.2, J20.2, J23.3, J24.3, R25.2, R27.1, R72.1, U38.2, U38.3; also elsewhere on the board
GNDA: C34.2, C35.2, C36.1, C39.2, C40.1, C43.2, C44.1, D5.2 (A2), D6.1 (A1), D10.1 (A1), D11.2 (A2), D13.1 (A1), D14.2 (A2), GD2.2, GD3.1, GD4.2, GD5.1, GD6.2, GD7.1, J3.2, J5.2, J6.2, J22.2, R27.2
HV+: J1.2; also elsewhere on the board
IGN: C47.1, R38.2; also elsewhere on the board
unnamed: D16.2 (A), J24.2
unnamed: D16.1 (K), PF3.1
unnamed: C33.1, D17.1 (A1), J23.2, PF3.2, R25.1, R160.2
unnamed: D40.2 (A), J24.1
unnamed: D40.1 (K), F2.1
unnamed: F5.1, GD3.2, J5.1
unnamed: F6.1, GD4.1, J5.3
unnamed: F7.1, GD5.2, J6.1
unnamed: F8.1, GD6.1, J6.3
unnamed: D24.2 (K), J9.1, PF1.1
unnamed: D24.1 (K), J9.2, R72.2
unnamed: F3.1, GD7.2, J3.1, J22.1
unnamed: F4.1, GD2.1, J3.3, J22.3
unnamed: JP3.2 (B), R37.1
unnamed: JP4.2 (B), R36.1
unnamed: JP5.2 (B), R35.1
unnamed: R26.2, R38.1, U38.4
unnamed: R160.1, U38.1
SW1-OUT: D28.1 (A1), J17.1; also elsewhere on the board
SW2-OUT: D37.1 (A1), J18.1; also elsewhere on the board
SW3-OUT: D38.1 (A1), J19.1; also elsewhere on the board
SW4-OUT: D39.1 (A1), J20.1; also elsewhere on the board

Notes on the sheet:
my vectrix has 12V always on, most units after 2008 (?) have buck disabled when ign off use this for those bikes https://github.com/kaminaris/GigaESC/tree/master/PowerBoard/TL494V2OC

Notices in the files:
kicad/Alarm.kicad_sch:
©CC-BY-NC
